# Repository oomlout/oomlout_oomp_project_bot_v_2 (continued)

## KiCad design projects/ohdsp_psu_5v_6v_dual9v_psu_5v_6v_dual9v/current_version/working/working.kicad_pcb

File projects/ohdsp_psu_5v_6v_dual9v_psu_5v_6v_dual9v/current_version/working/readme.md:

# psu_5v_6v_dual9v
 
## summary 
* id: ohdsp_psu_5v_6v_dual9v_psu_5v_6v_dual9v
* user: ohdsp
* name: psu_5v_6v_dual9v
* board: psu_5v_6v_dual9v
* repo: https://github.com/ohdsp/PSU-5V-6V-Dual9V
* src_file_repo_kicad_pcb: KiCad/PSU-5V-6V-Dual9V.kicad_pcb
* src_file_repo_kicad_pcb_link: https://github.com/ohdsp/PSU-5V-6V-Dual9V/tree/master/KiCad/PSU-5V-6V-Dual9V.kicad_pcb

* src_file_repo_sch: 
* src_file_repo_sch_link: https://github.com/ohdsp/PSU-5V-6V-Dual9V/tree/master/
* full details link: https://github.com/oomlout/oomlout_oomp_project_bot_v_2/tree/main/projects/ohdsp_psu_5v_6v_dual9v_psu_5v_6v_dual9v/current_version/working

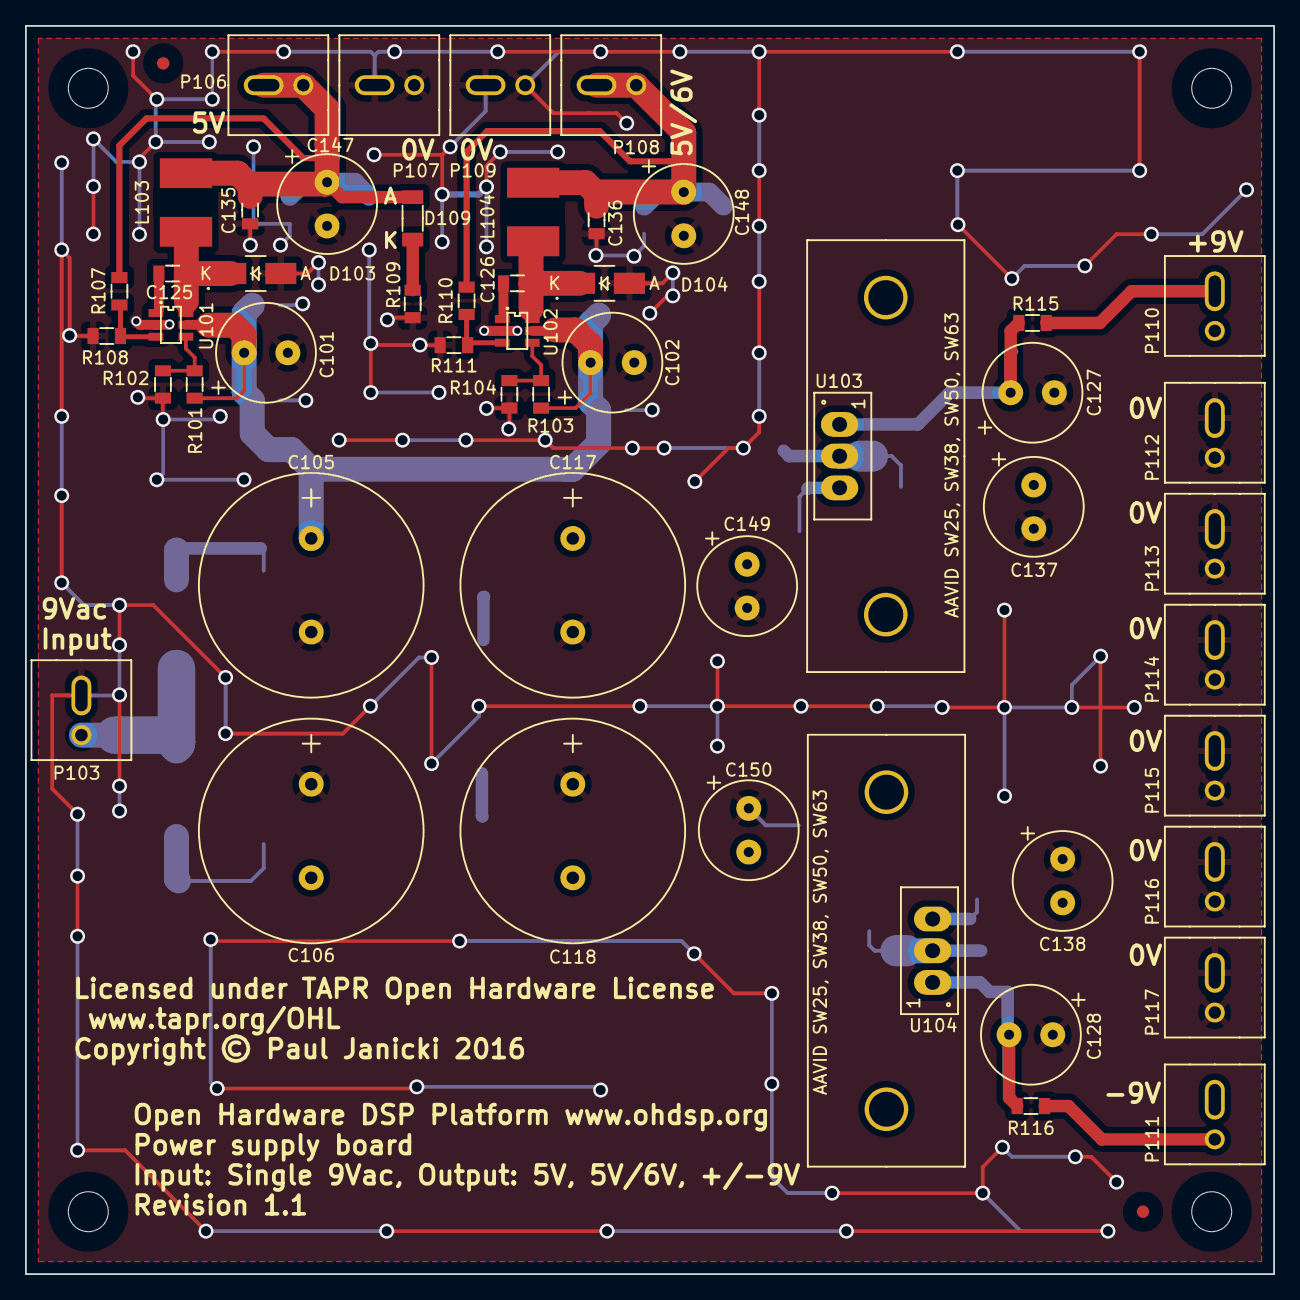
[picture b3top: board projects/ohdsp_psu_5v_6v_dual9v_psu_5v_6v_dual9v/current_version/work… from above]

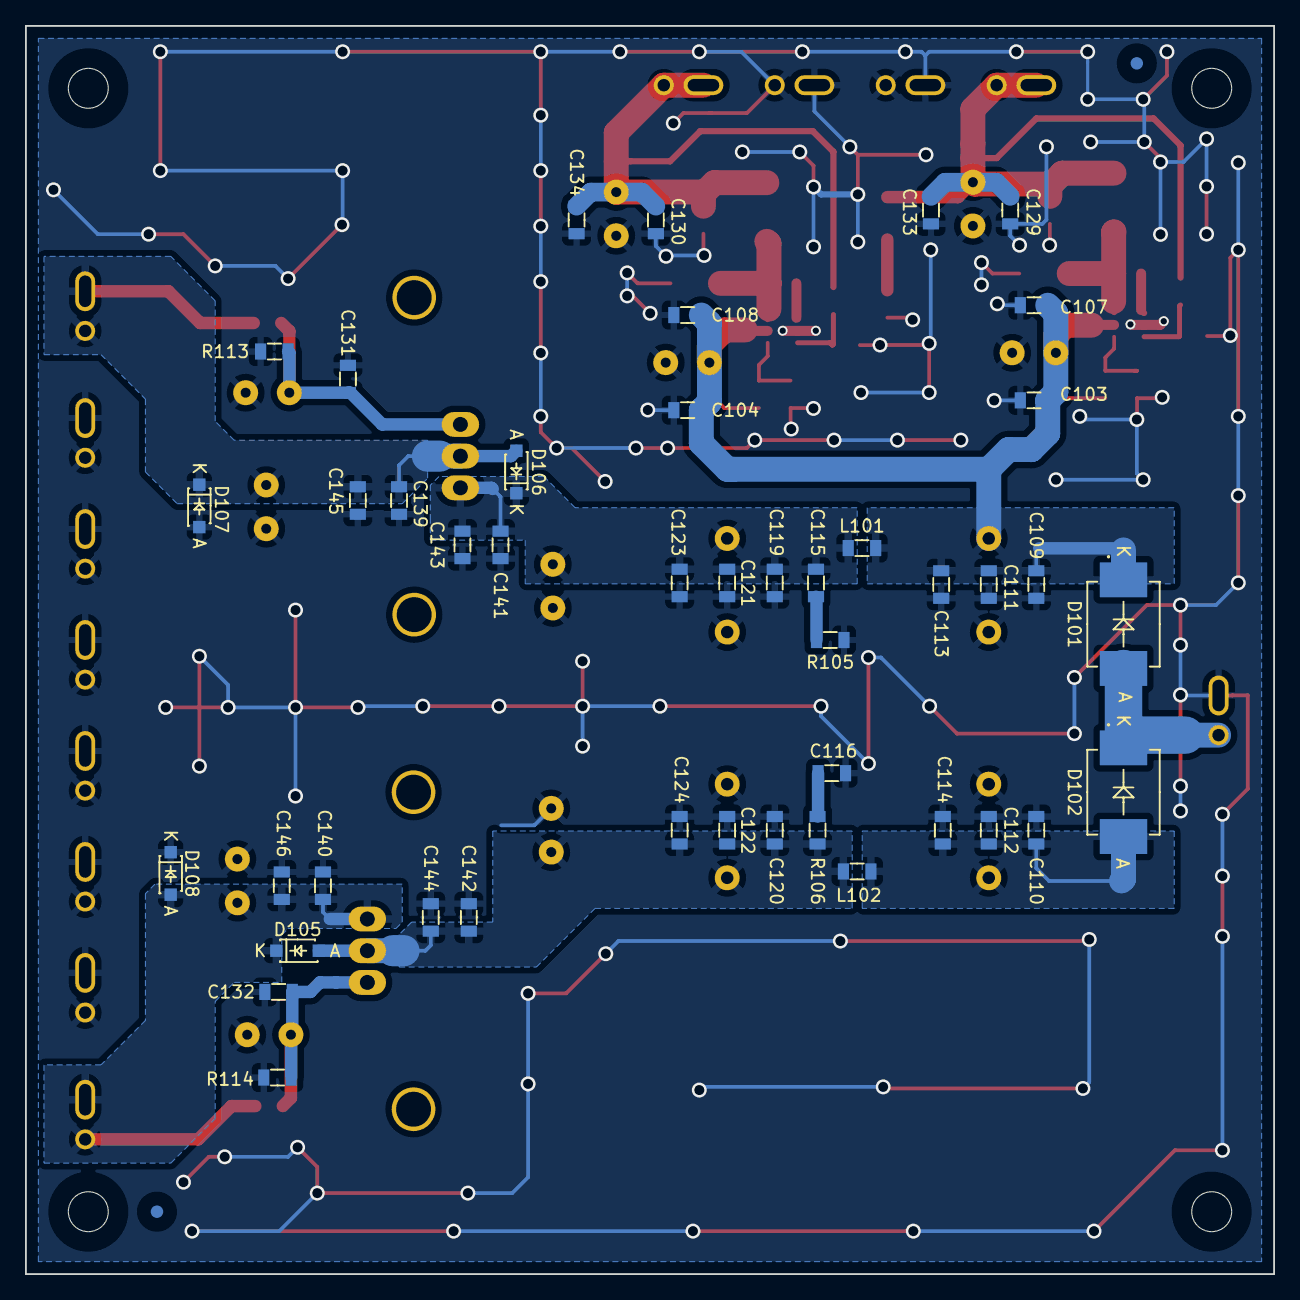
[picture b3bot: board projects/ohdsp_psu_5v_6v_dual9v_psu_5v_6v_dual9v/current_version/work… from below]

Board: 2 copper layers, 100.0 x 100.0 mm, 103 parts (46 on the bottom side), 23 nets.

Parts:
C101, C102, C127, C128, C137, C138, C147, C148, C149, C150: 220u; CAP-TH-D8mmP3.5mm
C103, C104, C109, C110, C119, C120, C129, C130, C133, C134, C141, C142, C145, C146: 22u; SMD-0805
C105, C106, C117, C118: 2200u; CAP-TH-D18mmP7.5mm
C107, C108, C111, C112, C121, C122, C131, C132, C135, C136, C139, C140, C143, C144: 100n; SMD-0805
C113, C114, C123, C124, C125, C126: 10n; SMD-0805
C115, C116: 100p; SMD-0805
D101, D102: ES3D; DIODE-SMC
D103, D104: B240A; DIODE-SMA
D105, D106, D107, D108: SS14L; DIODE-SOD-123
D109: Green LED 1206; SMD-1206
FID1, FID2, FID3, FID4: MNT_HOLE; FID-1MM-3MM
L101, L102: 600R@100MHz; SMD-0805
L103, L104: TYS50406R8M-10; IND-TYS5040-HS
MNT1, MNT2, MNT3, MNT4: MNT_HOLE; MNT_HOLE_3.2mm
P103, P106, P107, P108, P109, P110, P111, P112, P113, P114, P115, P116, P117: CONN_2x1; CONN-2WAY-2.54mm-3.81mm-SPACING
R101, R103: 475k; SMD-0805
R102, R104: 100k; SMD-0805
R105, R106: 47; SMD-0805
R107: 53k6; SMD-0805
R108, R111: 10k; SMD-0805
R109: 470; SMD-0805
R110: 66k5; SMD-0805
R113, R114: 750; SMD-0805
R115, R116: 120; SMD-0805
U101, U102: ADP2301AUJZ; IC-SOT23-6
U103: LM317; IC-TO220-HS-SW25-2G
U104: LM337; IC-TO220-HS-SW25-2G

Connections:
+5V: C129.1, C133.1, C135.1, C147.1, D109.1, L103.2, P106.1, P106.2, R107.1
GNDA: C101.2, C102.2, C103.2, C104.2, C105.2, C106.1, C107.2, C108.2, C109.2, C110.1, C111.2, C112.1, C113.2, C114.1, C116.1, C117.2, C118.1, C119.2, C120.1, C121.2, C122.1, C123.2, C124.1, C127.2, C128.1, C129.2, C130.2, C131.2, C132.1, C133.2, C134.2, C135.2, C136.2, C137.2, C138.1, C139.2, C140.1, C141.2, C142.1, C143.2, C144.1, C145.2, C146.1, C147.2, C148.2, C149.2, C150.1, D103.1, D104.1, D107.1, D108.2, P103.2, P107.1, P107.2, P109.1, P109.2, P112.1, P112.2, P113.1, P113.2, P114.1, P114.2, P115.1, P115.2, P116.1, P116.2, P117.1, P117.2, R102.2, R104.2, R105.2, R108.1, R109.1, R111.1, R113.1, R114.2, U101.2, U102.2
unnamed: C106.2, C110.2, C112.2, C114.2, D102.1, L102.1
unnamed: C115.1, C117.1, C119.1, C121.1, C123.1, C141.1, C143.1, C149.1, D106.2, L101.2, U103.3
unnamed: C115.2, R105.1
unnamed: C116.2, R106.1
unnamed: C118.2, C120.2, C122.2, C124.2, C142.2, C144.2, C150.2, D105.1, L102.2, R106.2, U104.2
unnamed: C125.1, D103.2, L103.1, U101.6
unnamed: C125.2, U101.1
unnamed: C126.1, D104.2, L104.1, U102.6
unnamed: C126.2, U102.1
unnamed: C127.1, C131.1, R113.2, R115.1, U103.1
unnamed: C128.2, C132.2, R114.1, R116.1, U104.1
unnamed: C130.1, C134.1, C136.1, C148.1, L104.2, P108.1, P108.2, R110.1
unnamed: C137.1, C139.1, C145.1, D106.1, D107.2, P110.1, P110.2, R115.2, U103.2
unnamed: C138.2, C140.2, C146.2, D105.2, D108.1, P111.1, P111.2, R116.2, U104.3
unnamed: D101.1, D102.2, P103.1
unnamed: D109.2, R109.2
unnamed: R101.1, R102.1, U101.4
unnamed: R103.1, R104.1, U102.4
unnamed: R107.2, R108.2, U101.3
unnamed: R110.2, R111.2, U102.3
VCC: C101.1, C102.1, C103.1, C104.1, C105.1, C107.1, C108.1, C109.1, C111.1, C113.1, D101.2, L101.1, R101.2, R103.2, U101.5, U102.5

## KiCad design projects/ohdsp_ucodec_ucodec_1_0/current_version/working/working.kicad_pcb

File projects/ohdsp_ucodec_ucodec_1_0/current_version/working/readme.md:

# ucodec
 
## summary 
* id: ohdsp_ucodec_ucodec_1_0
* user: ohdsp
* name: ucodec
* board: ucodec_1_0
* repo: https://github.com/ohdsp/uCODEC
* src_file_repo_kicad_pcb: KiCad/uCODEC-1.0.kicad_pcb
* src_file_repo_kicad_pcb_link: https://github.com/ohdsp/uCODEC/tree/master/KiCad/uCODEC-1.0.kicad_pcb

* src_file_repo_sch: 
* src_file_repo_sch_link: https://github.com/ohdsp/uCODEC/tree/master/
* full details link: https://github.com/oomlout/oomlout_oomp_project_bot_v_2/tree/main/projects/ohdsp_ucodec_ucodec_1_0/current_version/working

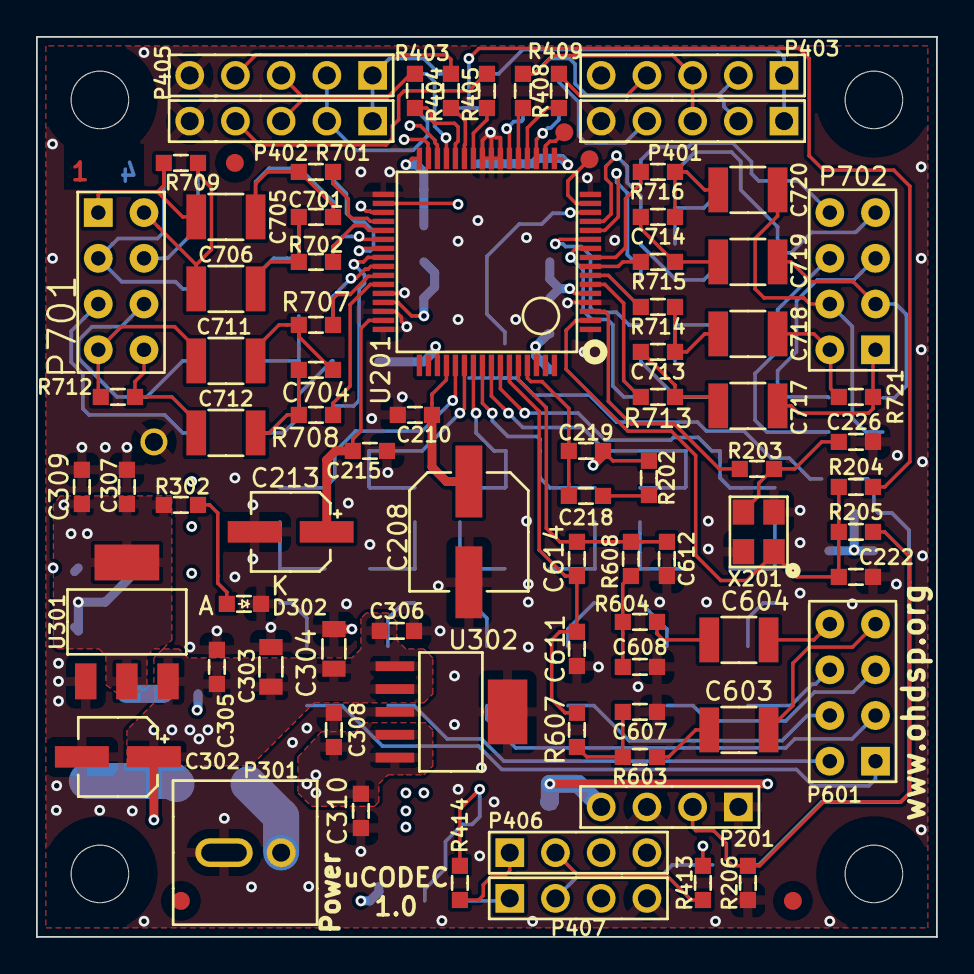
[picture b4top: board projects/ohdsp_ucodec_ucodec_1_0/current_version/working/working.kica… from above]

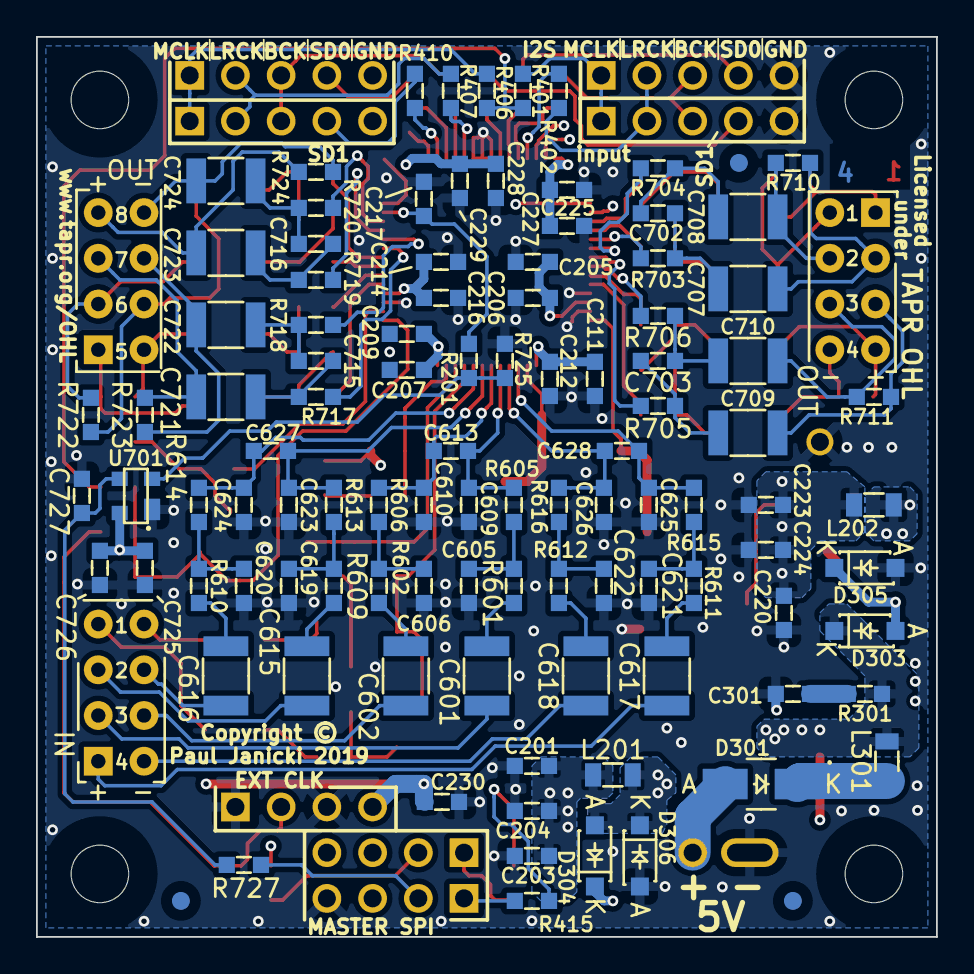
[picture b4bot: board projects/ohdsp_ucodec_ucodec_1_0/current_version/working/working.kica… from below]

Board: 4 copper layers, 50.0 x 50.0 mm, 194 parts (104 on the bottom side), 130 nets.

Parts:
C201, C220, C301, C605, C606, C607, C608, C613, C614, C619, C620, C621, C622, C627, C628: 100p; SMD-0603
C203, C223, C309, C310: 22u; SMD-0603
C204, C205, C207, C210, C211, C214, C215, C224, C225, C228, C230, C305, C306, C307, C308, C726: 100n; SMD-0603
C206, C209, C212, C216, C217, C227, C229, C727: 10n; SMD-0603
C208: 47u; CAP-SMD-SIZE-D
C213, C302: 10u; CAP-SMD-SIZE-B
C218: 39n; SMD-0603
C219: 2n2; SMD-0603
C222, C226: N/F; SMD-0603
C303, C304: 22u; SMD-0805
C601, C602, C603, C604, C615, C616, C617, C618, C705, C706, C707, C708, C709, C710, C711, C712, C717, C718, C719, C720, C721, C722, C723, C724: 1u; SMD-1210
C609, C610, C611, C612, C623, C624, C625, C626, C701, C702, C703, C704, C713, C714, C715, C716: 1n; SMD-0603
C725: 10u; SMD-0603
D301: B240A; DIODE-SMA
D302: LED 0603; SMD-0603-LED
D303, D304, D305, D306: 1N5819HW; DIODE-SOD-123
FID301, FID302, FID303, FID304, FID305, FID306: MNT_HOLE; FID-1MM-2MM
L201, L202, L301: 600R@100MHz; SMD-0805
MNT301, MNT302, MNT303, MNT304: MNT_HOLE; MNT_HOLE_3.2mm
P201, P406, P407: CONN_4x1; CONN_SIL_4_1MM
P301: CONN_2x1; CONN-2WAY-2.54mm-3.81mm-SPACING
P401, P402, P403, P405: CONN_5x1; CONN_SIL_5_1MM
P404, P408: PIN; TP-1mm
P601, P701, P702: CONN_02X04; CONN_DIL_2X04
R201, R204, R404, R405, R413, R415: 22; SMD-0603
R202: 3K32; SMD-0603
R203, R205, R206, R406, R414: N/F; SMD-0603
R301: 47; SMD-0603
R302: 470; SMD-0603
R401, R402, R403, R407, R408, R409, R410: 0; SMD-0603
R601, R602, R603, R604, R609, R610, R611, R612, R701, R702, R703, R704, R705, R706, R707, R708, R713, R714, R715, R716, R717, R718, R719, R720: 1K; SMD-0603
R605, R606, R607, R608, R613, R614, R615, R616: 220; SMD-0603
R709, R710, R711, R712, R721, R722, R723, R724: 220K; SMD-0603
R725: 100K; SMD-0603
R727: 100; SMD-0603
TP401: PIN; TP-TH-1mm
U201: AD1939; IC-LQFP64
U301: TLV1117LV33DCY; IC-SOT-223
U302: TPS7A4533DCQ; IC-SOT223-6
U701: CAT811TTBI; IC-SOT143
X201: N/F; XTAL_3.2x2.5_4PIN

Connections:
+3.3VA: C308.1, C310.1, D304.1, D306.2, L201.1, U302.4, U302.5
+3V3: C230.1, C307.1, C309.1, C725.1, C726.1, D303.1, D305.2, L202.1, P201.4, R302.1, U301.2, U701.4
+5V: C302.1, C303.1, C304.1, C305.1, C306.1, D303.2, D304.2, L301.2, R301.1, U301.3, U302.1, U302.2
/AD1939/AVDD: C201.1, C203.1, C204.1, C205.1, C206.1, C207.1, C209.1, C211.1, C212.1, C214.1, C216.1, C219.2, L201.2, R202.2, U201.5, U201.45, U201.51, U201.62
/AD1939/DVDD: C220.1, C223.1, C224.1, C225.1, C227.1, C228.1, C229.1, L202.2, U201.17, U201.32
/AD1939/XTALIN: C222.1, R204.1, R205.1, U201.2, X201.1
/AD1939/XTALOUT: R203.1, U201.3
/ADC1LN: C626.2, C628.2, R616.1, U201.54
/ADC1LP: C625.1, C628.1, R615.1, U201.53
/ADC1RN: C610.2, C613.2, R606.1, U201.56
/ADC1RP: C609.1, C613.1, R605.1, U201.55
/ADC2LN: C624.2, C627.2, R614.1, U201.58
/ADC2LP: C623.1, C627.1, R613.1, U201.57
/ADC2RN: C612.2, C614.2, R608.1, U201.60
/ADC2RP: C611.1, C614.1, R607.1, U201.59
/ADC Passive Filters/IN1N: C618.2, P601.2
/ADC Passive Filters/IN1P: C617.2, P601.1
/ADC Passive Filters/IN2N: C602.2, P601.4
/ADC Passive Filters/IN2P: C601.2, P601.3
/ADC Passive Filters/IN3N: C616.2, P601.6
/ADC Passive Filters/IN3P: C615.2, P601.5
/ADC Passive Filters/IN4N: C604.2, P601.8
/ADC Passive Filters/IN4P: C603.2, P601.7
/CM: C208.1, C210.1, U201.52
/CODEC_RST: R201.2, R725.1, U701.2
/DAC1LN: R702.1, U201.37
/DAC1LP: R701.2, U201.36
/DAC1RN: R704.1, U201.39
/DAC1RP: R703.2, U201.38
/DAC2LN: R706.1, U201.41
/DAC2LP: R705.2, U201.40
/DAC2RN: R708.1, U201.43
/DAC2RP: R707.2, U201.42
/DAC3LN: R714.1, U201.7
/DAC3LP: R713.2, U201.6
/DAC3RN: R716.1, U201.9
/DAC3RP: R715.2, U201.8
/DAC4LN: R718.1, U201.11
/DAC4LP: R717.2, U201.10
/DAC4RN: R720.1, U201.13
/DAC4RP: R719.2, U201.12
/DAC Passive Filters/OUT1N: C706.1, P701.2, R709.2
/DAC Passive Filters/OUT1P: C705.1, P701.1, R709.1
/DAC Passive Filters/OUT2N: C708.1, P701.4, R710.2
/DAC Passive Filters/OUT2P: C707.1, P701.3, R710.1
/DAC Passive Filters/OUT3N: C710.1, P701.6, R711.2
/DAC Passive Filters/OUT3P: C709.1, P701.5, R711.1
/DAC Passive Filters/OUT4N: C712.1, P701.8, R712.2
/DAC Passive Filters/OUT4P: C711.1, P701.7, R712.1
/DAC Passive Filters/OUT5N: C718.1, P702.2, R721.2
/DAC Passive Filters/OUT5P: C717.1, P702.1, R721.1
/DAC Passive Filters/OUT6N: C720.1, P702.4, R722.2
/DAC Passive Filters/OUT6P: C719.1, P702.3, R722.1
/DAC Passive Filters/OUT7N: C722.1, P702.6, R723.2
/DAC Passive Filters/OUT7P: C721.1, P702.5, R723.1
/DAC Passive Filters/OUT8N: C724.1, P702.8, R724.2
/DAC Passive Filters/OUT8P: C723.1, P702.7, R724.1
/GLB_RESET: P407.2, R727.2
/IN_BCLK0: R403.2, U201.28
/IN_LRCLK0: R402.2, U201.29
/IN_SDATA0: R404.2, U201.27
/IN_SDATA1: R405.2, U201.26
/MCLK: R204.2, R401.2, R406.2
/OUT_BCLK0: R408.1, U201.21
/OUT_LRCLK0: R407.1, U201.22
/OUT_SDATA0: R409.1, U201.20
/OUT_SDATA1: R410.1, U201.19
/OUT_SDATA2: P404.1, U201.18
/OUT_SDATA3: P408.1, U201.15
/SPI_M_CLK: P406.3, U201.34
/SPI_M_CS: R414.2, R415.2, U201.35
/SPI_M_MISO: R413.2, U201.31
/SPI_M_MOSI: P406.4, U201.30
GNDD: C201.2, C203.2, C204.2, C205.2, C206.2, C207.2, C208.2, C209.2, C210.2, C211.2, C212.2, C213.2, C214.2, C215.2, C216.2, C217.2, C220.2, C222.2, C223.2, C224.2, C225.2, C226.2, C227.2, C228.2, C229.2, C230.2, C301.2, C302.2, C303.2, C304.2, C305.2, C306.2, C307.2, C308.2, C309.2, C310.2, C605.2, C606.2, C607.2, C608.2, C609.2, C610.1, C611.2, C612.1, C619.2, C620.2, C621.2, C622.2, C623.2, C624.1, C625.2, C626.1, C725.2, C726.2, C727.2, D302.2, D305.1, D306.1, P201.1, P201.3, P301.2, P401.5, P402.5, P403.5, P405.5, P407.4, R206.1, R725.2, TP401.1, U201.1, U201.4, U201.16, U201.23, U201.24, U201.25, U201.33, U201.44, U201.46, U201.48, U301.1, U302.3, U701.1, X201.2, X201.4
unnamed: C213.1, C215.1, U201.47
unnamed: C217.1, R201.1, U201.14
unnamed: C218.1, C219.1, U201.61
unnamed: C218.2, R202.1
unnamed: C226.1, R203.2, X201.3
unnamed: C301.1, R301.2
unnamed: C601.1, R601.2
unnamed: C602.1, R602.2
unnamed: C603.1, R603.2
unnamed: C604.1, R604.2
unnamed: C605.1, R601.1, R605.2
unnamed: C606.1, R602.1, R606.2
unnamed: C607.1, R603.1, R607.2
unnamed: C608.1, R604.1, R608.2
unnamed: C615.1, R609.2
unnamed: C616.1, R610.2
unnamed: C617.1, R611.2
unnamed: C618.1, R612.2
unnamed: C619.1, R609.1, R613.2
unnamed: C620.1, R610.1, R614.2
unnamed: C621.1, R611.1, R615.2
unnamed: C622.1, R612.1, R616.2
unnamed: C701.1, C705.2, R701.1
unnamed: C701.2, C706.2, R702.2
unnamed: C702.1, C707.2, R703.1
unnamed: C702.2, C708.2, R704.2
unnamed: C703.1, C709.2, R705.1
unnamed: C703.2, C710.2, R706.2
unnamed: C704.1, C711.2, R707.1
unnamed: C704.2, C712.2, R708.2
unnamed: C713.1, C717.2, R713.1
unnamed: C713.2, C718.2, R714.2
unnamed: C714.1, C719.2, R715.1
unnamed: C714.2, C720.2, R716.2
unnamed: C715.1, C721.2, R717.1
unnamed: C715.2, C722.2, R718.2
unnamed: C716.1, C723.2, R719.1
unnamed: C716.2, C724.2, R720.2
unnamed: C727.1, R727.1, U701.3
unnamed: D301.1, P301.1
unnamed: D301.2, L301.1
unnamed: D302.1, R302.2
unnamed: P201.2, R205.2, R206.2
unnamed: P401.1, P403.1, R406.1
unnamed: P401.2, P403.2, R407.2
unnamed: P401.3, P403.3, R408.2
unnamed: P401.4, R410.2
unnamed: P402.1, P405.1, R401.1
unnamed: P402.2, P405.2, R402.1
unnamed: P402.3, P405.3, R403.1
unnamed: P402.4, R405.1
unnamed: P403.4, R409.2
unnamed: P405.4, R404.1
unnamed: P406.1, R414.1
unnamed: P406.2, R413.1
unnamed: P407.1, R415.1

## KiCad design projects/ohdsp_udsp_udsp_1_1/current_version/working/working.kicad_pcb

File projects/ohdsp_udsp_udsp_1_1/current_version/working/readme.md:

# udsp
 
## summary 
* id: ohdsp_udsp_udsp_1_1
* user: ohdsp
* name: udsp
* board: udsp_1_1
* repo: https://github.com/ohdsp/uDSP
* src_file_repo_kicad_pcb: KiCad/uDSP-1.1.kicad_pcb
* src_file_repo_kicad_pcb_link: https://github.com/ohdsp/uDSP/tree/master/KiCad/uDSP-1.1.kicad_pcb

* src_file_repo_sch: 
* src_file_repo_sch_link: https://github.com/ohdsp/uDSP/tree/master/
* full details link: https://github.com/oomlout/oomlout_oomp_project_bot_v_2/tree/main/projects/ohdsp_udsp_udsp_1_1/current_version/working

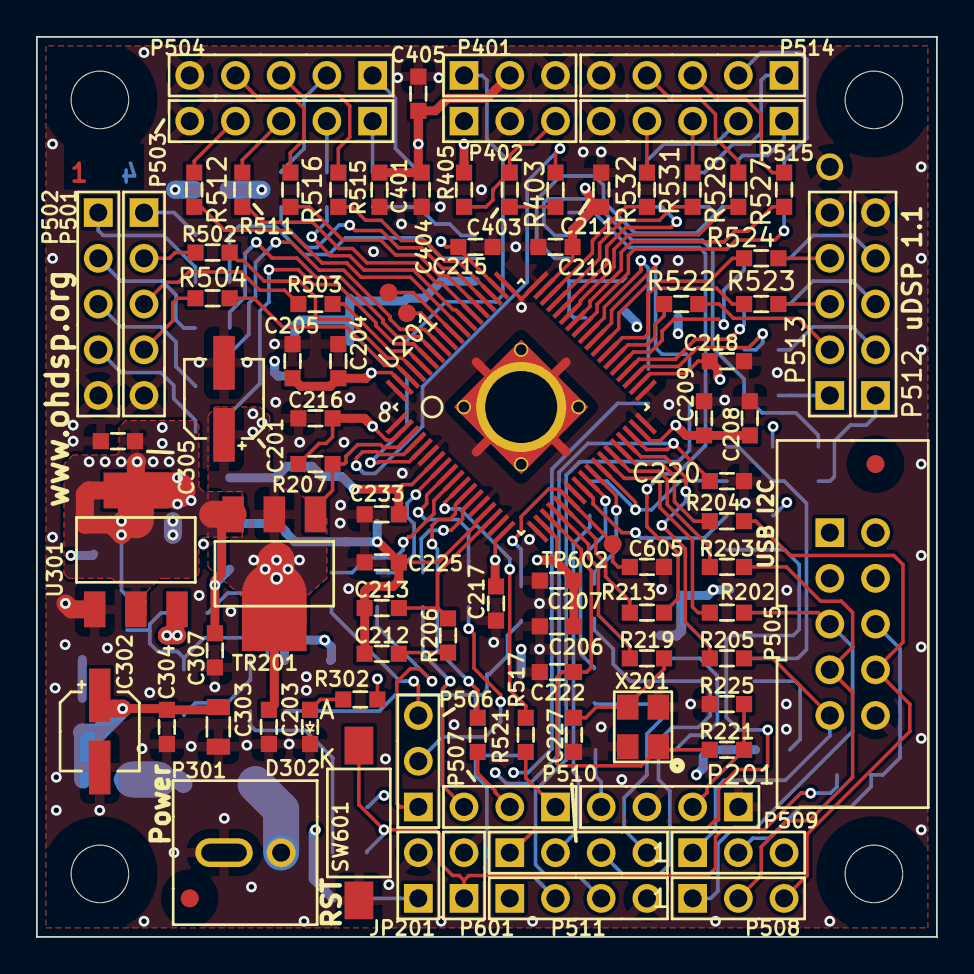
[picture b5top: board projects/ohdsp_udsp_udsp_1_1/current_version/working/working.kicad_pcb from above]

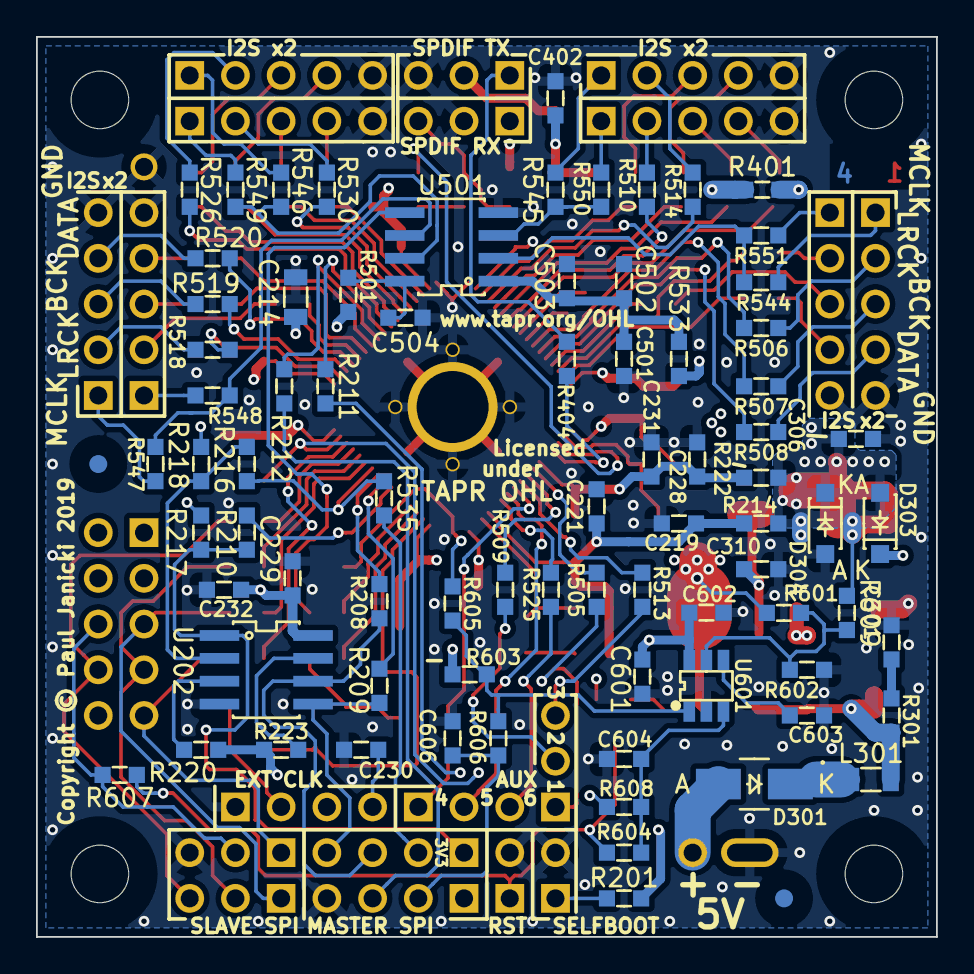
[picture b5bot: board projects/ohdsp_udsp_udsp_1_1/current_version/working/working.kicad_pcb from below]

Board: 4 copper layers, 50.0 x 50.0 mm, 177 parts (80 on the bottom side), 133 nets.

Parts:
C201: 22u; CAP-SMD-SIZE-B
C203, C204, C206, C208, C210, C215, C216, C217, C218, C225, C229, C230, C233, C304, C305, C307, C404, C405, C503, C602, C605, C606: 100n; SMD-0603
C205, C207, C209, C211, C220, C403, C603, C604: 10n; SMD-0603
C212: 5n6; SMD-0603
C213: 150p; SMD-0603
C214: 10u; SMD-0805
C219, C228, C301, C401, C501: 100p; SMD-0603
C221, C231, C232, C310, C601: 10u; SMD-0603
C222, C227: 33p; SMD-0603
C302: 10u; CAP-SMD-SIZE-B
C303: 22u; SMD-0805
C306, C402, C502: 22u; SMD-0603
C504: 1n; SMD-0603
D301: B240A; DIODE-SMA
D302: LED 0603; SMD-0603-LED
D303, D304: 1N5819HW; DIODE-SOD-123
FID301, FID302, FID303, FID304: MNT_HOLE; FID-1MM-3MM
JP201: CONN_2x1; CONN_SIL_2_1MM
L301: 600R@100MHz; SMD-0805
MNT301, MNT302, MNT303, MNT304: MNT_HOLE; MNT_HOLE_3.2mm
P201, P510, P511: CONN_4x1; CONN_SIL_4_1MM
P301: CONN_2x1; CONN-2WAY-2.54mm-3.81mm-SPACING
P401, P402, P506, P507, P508, P509: CONN_3x1; CONN_SIL_3_1MM
P501, P502, P503, P504, P512, P513, P514, P515: CONN_5x1; CONN_SIL_5_1MM
P505: CONN_02X05; CONN_DIL_2X5_BOX_1MM
P601: CONN_2x1; CONN_SIL_2_1MM
R201, R207, R501: 1K; SMD-0603
R202, R208, R209, R210, R211, R212, R213, R216, R403, R404, R518, R519, R520, R522, R523, R524, R526, R527, R528, R530, R531, R532, R544, R545, R546, R547, R548, R549, R550, R551: 22; SMD-0603
R203, R204, R205, R502, R503, R504, R506, R507, R508, R510, R511, R512, R514, R515, R516, R535, R607: 0; SMD-0603
R206: 4k3; SMD-0603
R214, R222, R401, R533: 1; SMD-0603
R217, R220, R223, R405, R602: 10K; SMD-0603
R218, R221, R225, R609: N/F; SMD-0603
R219, R604, R605, R606: 100; SMD-0603
R301: 47; SMD-0603
R302: 470; SMD-0603
R505, R509, R513, R517, R521, R525: 4K7; SMD-0603
R601: 18K7; SMD-0603
R603, R608: 2K2; SMD-0603
SW601: FSMSM; SW_TACT_SMD_FSMSM
TP201, TP202, TP602: PIN; TP-1mm
TP502: PIN; TP-TH-1mm
TR201: NJT4030PT3G; IC-SOT-223
U201: ADAU1452WBCPZ; IC-LFCSP72-HANDFIT
U202: M95M01-RMN6TP; IC_SOIC_8
U301: TLV1117LV33DCY; IC-SOT-223
U501: NB3L553; IC_SOIC_8
U601: NCP308SNADJT1G; IC-SOT23-6
X201: 24M576; XTAL_3.2x2.5_4PIN

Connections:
+1V2: C201.1, C203.1, C204.1, C205.1, C206.1, C207.1, C208.1, C209.1, C210.1, C211.1, R601.1, TR201.2, U201.20, U201.35, U201.53, U201.71
+3V3: C214.1, C215.1, C216.1, C217.1, C218.1, C229.1, C230.1, C232.1, C305.1, C306.1, C307.1, C310.1, C601.1, C602.1, D303.1, D304.2, P201.4, R201.1, R207.1, R214.2, R217.2, R218.2, R220.2, R222.2, R223.2, R302.1, R401.2, R501.1, R533.2, R603.1, R608.1, R609.1, TR201.3, U201.2, U201.18, U201.38, U201.56, U202.8, U301.2, U601.6
/AUXADC1: R505.2, U201.8
/AUXADC2: R509.2, U201.9
/AUXADC3: R513.2, U201.10
/AUXADC4: R517.2, U201.11
/AUXADC5: R521.2, U201.12
/AUXADC6: R525.2, U201.13
/Connectors/MCLKA1: P504.1, R545.2
/Connectors/MCLKA2: P503.1, R550.2
/Connectors/MCLKA3: P502.1, R544.2
/Connectors/MCLKA4: P501.1, R551.2
/Connectors/MCLKB1: P512.1, R547.2
/Connectors/MCLKB2: P513.1, R548.2
/Connectors/MCLKB3: P514.1, R546.2
/Connectors/MCLKB4: P515.1, R549.2
/DSP/AVDD: C228.1, C231.1, C233.1, R222.1, U201.7
/DSP/MCLK_ADAU: R213.1, U201.23
/DSP/MISO_SDA: R202.2, U201.30
/DSP/MOSI_ADDR1: R204.2, U201.32
/DSP/PVDD: C212.1, C213.1, C219.1, C221.1, C225.1, R214.1, U201.15
/DSP/SCLK_SCL: R203.2, U201.31
/DSP/SELFBOOT: C220.1, JP201.1, R201.2, U201.34
/DSP/SS_ADDR0: R205.2, U201.33
/DSP/XTALIN: C222.1, R221.1, U201.21, X201.1
/DSP/XTALOUT: R219.1, U201.22
/DSP_RESET: C605.1, R605.2, TP602.1, U201.24
/GLB_RESET: C606.1, P511.2, R606.2
/IN_BCLK0: R515.2, U201.57
/IN_BCLK1: R511.2, U201.60
/IN_BCLK2: R507.2, U201.65
/IN_BCLK3: R503.2, U201.68
/IN_LRCLK0: R514.2, U201.58
/IN_LRCLK1: R510.2, U201.61
/IN_LRCLK2: R506.2, U201.66
/IN_LRCLK3: R502.2, U201.69
/IN_SDATA0: R516.2, U201.59
/IN_SDATA1: R512.2, U201.62
/IN_SDATA2: R508.2, U201.67
/IN_SDATA3: R504.2, U201.70
/MAN_RESET: P505.6, P509.2, R607.2
/MCLK: R213.2, U501.5
/OUT_BCLK0: R519.1, U201.40
/OUT_BCLK1: R523.1, U201.43
/OUT_BCLK2: R527.1, U201.48
/OUT_BCLK3: R531.1, U201.51
/OUT_LRCLK0: R518.1, U201.39
/OUT_LRCLK1: R522.1, U201.42
/OUT_LRCLK2: R526.1, U201.47
/OUT_LRCLK3: R530.1, U201.50
/OUT_SDATA0: R520.1, U201.41
/OUT_SDATA1: R524.1, U201.44
/OUT_SDATA2: R528.1, U201.49
/OUT_SDATA3: R532.1, U201.52
/SPDIF/SPDIF_3V3: C401.1, C402.1, C404.1, C405.1, P401.2, P402.1, R401.1, R405.2
/SPDIF_RX: R403.2, U201.4
/SPDIF_TX: R404.2, U201.5
/SPI_MISO: P505.5, P508.1, R202.1
/SPI_MOSI: P505.8, P508.3, R204.1
/SPI_M_CLK: P510.3, R208.2, U202.6
/SPI_M_CS1: P510.1, R210.2, R217.1, U202.1
/SPI_M_CS2: P511.1, R211.2
/SPI_M_MISO: R216.1, R535.2, U201.29
/SPI_M_MOSI: P510.4, R209.2, U202.5
/SPI_M_MUTE: P511.3, R212.2
/SPI_SCLK: P505.7, P508.2, R203.1
/SPI_SS: P505.9, P509.1, R205.1
GNDD: C201.2, C203.2, C204.2, C205.2, C206.2, C207.2, C208.2, C209.2, C210.2, C211.2, C214.2, C215.2, C216.2, C217.2, C218.2, C219.2, C220.2, C221.2, C222.2, C225.2, C227.2, C228.2, C229.2, C230.2, C231.2, C232.2, C233.2, C301.2, C302.2, C303.2, C304.2, C305.2, C306.2, C307.2, C310.2, C401.2, C402.2, C404.2, C405.2, C501.2, C502.2, C503.2, C504.2, C601.2, C602.2, C603.2, C604.2, C605.2, C606.2, D302.2, D304.1, JP201.2, P201.1, P201.3, P301.2, P401.3, P402.2, P501.5, P502.5, P503.5, P504.5, P505.10, P509.3, P511.4, P512.5, P513.5, P514.5, P515.5, P601.2, R225.1, R602.2, SW601.2, TP502.1, U201.1, U201.6, U201.14, U201.17, U201.19, U201.25, U201.36, U201.37, U201.54, U201.55, U201.72, U201.EP1, U202.4, U301.1, U501.4, U601.2, X201.2, X201.4
unnamed: C212.2, R206.1
unnamed: C213.2, R206.2, U201.16
unnamed: C227.1, R219.2, X201.3
unnamed: C301.1, R301.2
unnamed: C403.1, R403.1
unnamed: C403.2, P402.3, R405.1
unnamed: C501.1, C502.1, C503.1, R533.1, U501.1
unnamed: C504.1, R501.2, U501.8
unnamed: C603.1, U601.4
unnamed: C604.1, R604.1, R608.2, U601.3
unnamed: D301.1, P301.1
unnamed: D301.2, L301.1
unnamed: D302.1, R302.2
unnamed: P201.2, R221.2, R225.2
unnamed: P401.1, R404.1
unnamed: P501.2, R502.1
unnamed: P501.3, R503.1
unnamed: P501.4, R504.1
unnamed: P502.2, R506.1
unnamed: P502.3, R507.1
unnamed: P502.4, R508.1
unnamed: P503.2, R510.1
unnamed: P503.3, R511.1
unnamed: P503.4, R512.1
unnamed: P504.2, R514.1
unnamed: P504.3, R515.1
unnamed: P504.4, R516.1
unnamed: P506.1, R505.1
unnamed: P506.2, R509.1
unnamed: P506.3, R513.1
unnamed: P507.1, R517.1
unnamed: P507.2, R521.1
unnamed: P507.3, R525.1
unnamed: P510.2, R535.1
unnamed: P512.2, R518.2
unnamed: P512.3, R519.2
unnamed: P512.4, R520.2
unnamed: P513.2, R522.2
unnamed: P513.3, R523.2
unnamed: P513.4, R524.2
unnamed: P514.2, R526.2
unnamed: P514.3, R527.2
unnamed: P514.4, R528.2
unnamed: P515.2, R530.2
unnamed: P515.3, R531.2
unnamed: P515.4, R532.2
unnamed: P601.1, R604.2, R607.1, SW601.1
unnamed: R207.2, TR201.1, U201.3
unnamed: R208.1, U201.28
unnamed: R209.1, U201.27
unnamed: R210.1, U201.26
unnamed: R211.1, U201.46
unnamed: R212.1, U201.45
unnamed: R216.2, R218.1, U202.2
unnamed: R220.1, U202.3
unnamed: R223.1, U202.7
unnamed: R544.1, R551.1, U501.2
unnamed: R545.1, R550.1, U501.3
unnamed: R546.1, R549.1, U501.7
unnamed: R547.1, R548.1, U501.6
unnamed: R601.2, R602.1, R609.2, U601.5
unnamed: R603.2, R605.1, R606.1, U601.1
unnamed: TP201.1, U201.64
unnamed: TP202.1, U201.63
VCC: C302.1, C303.1, C304.1, D303.2, L301.2, R301.1, U301.3

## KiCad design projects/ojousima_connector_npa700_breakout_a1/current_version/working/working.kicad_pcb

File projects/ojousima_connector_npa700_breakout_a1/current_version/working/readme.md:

# connector
 
## summary 
* id: ojousima_connector_npa700_breakout_a1
* user: ojousima
* name: connector
* board: npa700_breakout_a1
* repo: https://github.com/ojousima/connector
* src_file_repo_kicad_pcb: npa700-breakout-a1/npa700-breakout-a1.kicad_pcb
* src_file_repo_kicad_pcb_link: https://github.com/ojousima/connector/tree/master/npa700-breakout-a1/npa700-breakout-a1.kicad_pcb

* src_file_repo_sch: npa700-breakout-a1/npa700-breakout-a1.sch
* src_file_repo_sch_link: https://github.com/ojousima/connector/tree/master/npa700-breakout-a1/npa700-breakout-a1.sch
* full details link: https://github.com/oomlout/oomlout_oomp_project_bot_v_2/tree/main/projects/ojousima_connector_npa700_breakout_a1/current_version/working

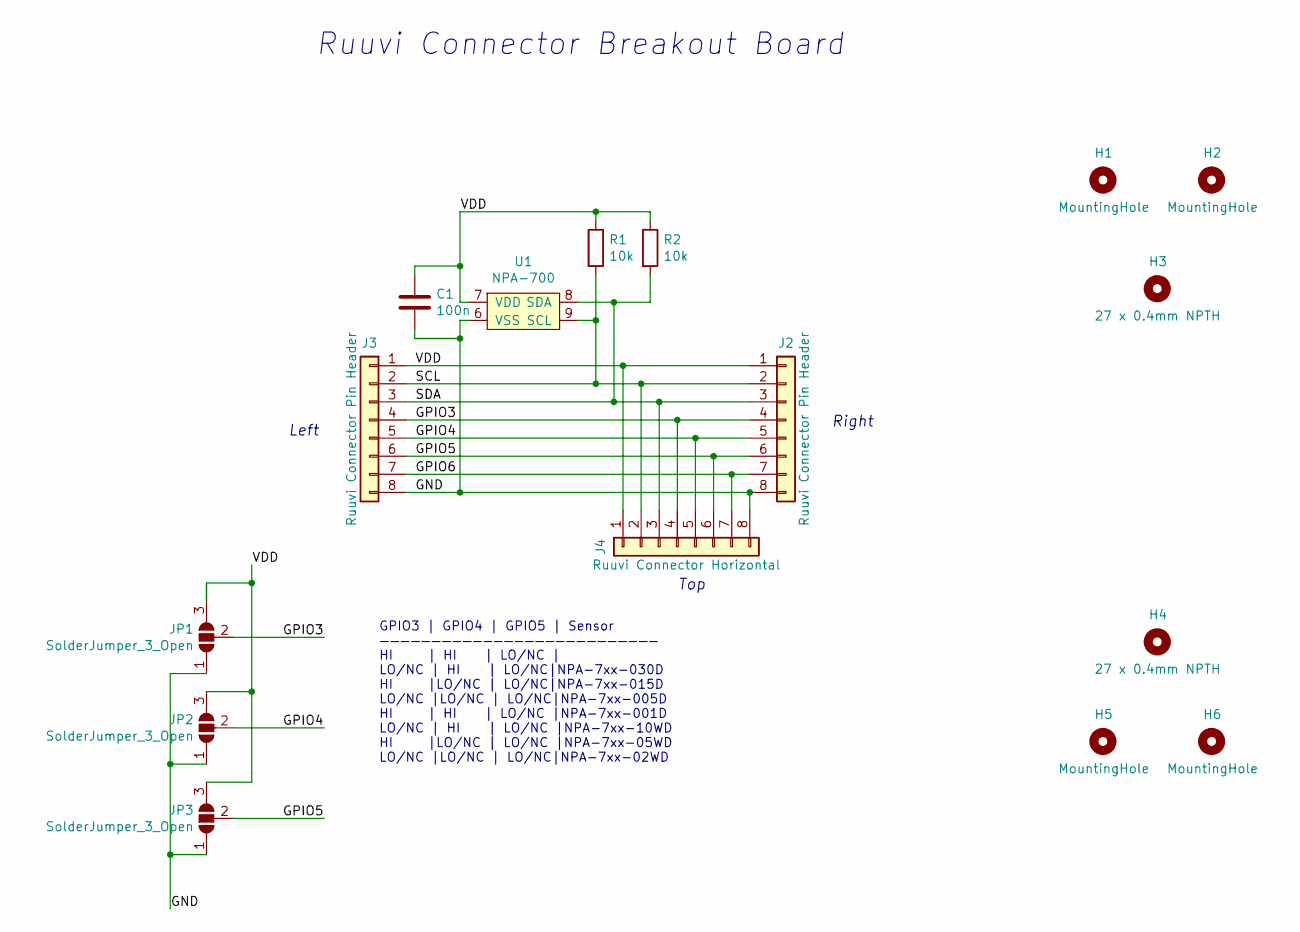
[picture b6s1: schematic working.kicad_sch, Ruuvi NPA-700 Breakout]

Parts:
C1: 100n; CAPC160X80X35L25N
H1, H2, H5, H6: MountingHole; MountingHole_3.2mm_M3_Pad_Via
H3, H4: 27 x 0.4mm NPTH; BreakoutHoles
J2, J3: Ruuvi Connector Pin Header; RUUVI_CONNECTOR_8PIN_HEADER
J4: Ruuvi Connector Horizontal; RUUVI_CONNECTOR_FFC
JP1, JP2, JP3: SolderJumper_3_Open; SolderJumper-3_P2.0mm_Open_TrianglePad1.0x1.5mm_NumberLabels
R1, R2: 10k; CAPC160X80X35L25N
U1: NPA-700; SOIC-14W_7.5x9mm_P1.27mm

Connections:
/GND: C1.1, J2.8, J3.8, J4.8, JP1.1 (A), JP2.1 (A), JP3.1 (A), U1.6 (VSS)
/GPIO3: J2.4, J3.4, J4.4, JP1.2 (C)
/GPIO4: J2.5, J3.5, J4.5, JP2.2 (C)
/GPIO5: J2.6, J3.6, J4.6, JP3.2 (C)
/GPIO6: J2.7, J3.7, J4.7
/SCL: J2.2, J3.2, J4.2, R1.2, U1.9 (SCL)
/SDA: J2.3, J3.3, J4.3, R2.2, U1.8 (SDA)
/VDD: C1.2, J2.1, J3.1, J4.1, JP1.3 (B), JP2.3 (B), JP3.3 (B), R1.1, R2.1, U1.7 (VDD)

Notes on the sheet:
Left
Right
Ruuvi Connector Breakout Board
GPIO3 | GPIO4 | GPIO5 | Sensor ——————————————————————————— HI | HI | LO/NC | LO/NC | HI | LO/NC|NPA-7xx-030D HI |LO/NC | LO/NC|NPA-7xx-015D LO/NC |LO/NC | LO/NC|NPA-7xx-005D HI | HI | LO/NC |NPA-7xx-001D LO/NC | HI | LO/NC |NPA-7xx-10WD HI |LO/NC | LO/NC |NPA-7xx-05WD LO/NC |LO/NC | LO/NC|NPA-7xx-0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
Top

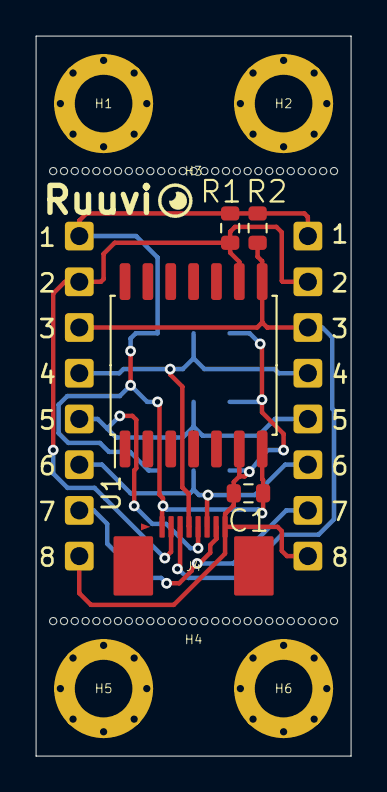
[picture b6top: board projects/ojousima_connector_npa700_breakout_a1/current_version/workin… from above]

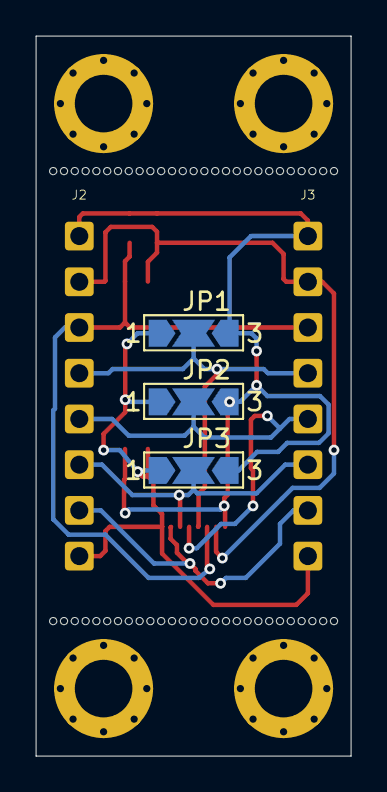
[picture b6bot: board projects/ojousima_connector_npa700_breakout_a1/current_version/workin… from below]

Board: 2 copper layers, 17.5 x 40.0 mm, 16 parts (5 on the bottom side), 8 nets.
